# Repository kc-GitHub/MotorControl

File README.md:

Firmware HM Motor-Control
===================================

#Changelog#

## First Version: 0.01 (Beta)##
 * First Commit

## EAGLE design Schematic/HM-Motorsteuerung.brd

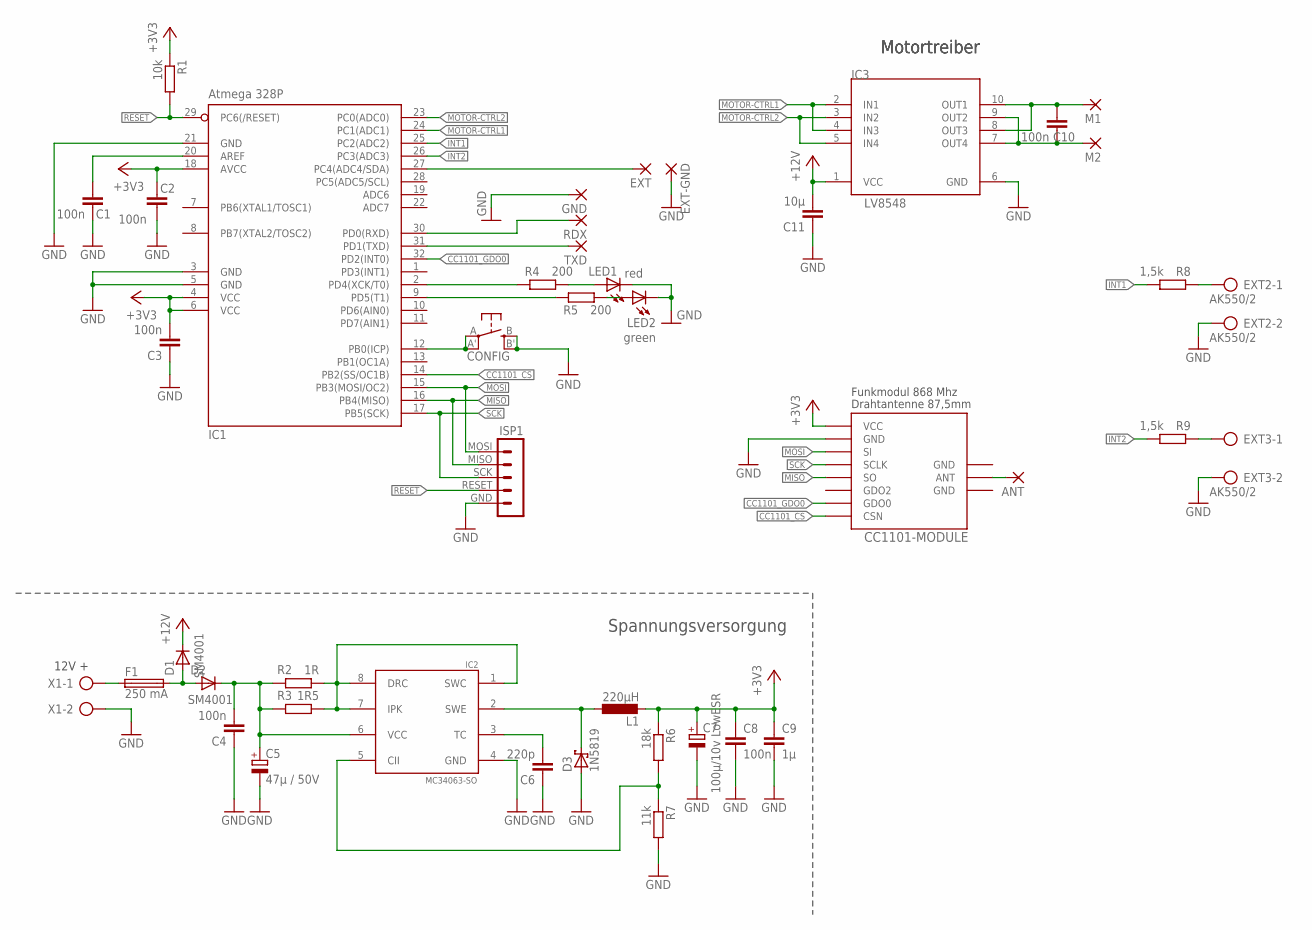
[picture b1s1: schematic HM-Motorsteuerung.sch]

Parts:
ANT: 1,6/0,8
C1, C2, C3, C4, C8, C10: 100n; C0805
C5: 47µ / 50V; E2,5-7
C6: 220p; C0805
C7: 100µ/10v LowESR; SMC_D
C9: 1µ; C0805
C11: 10µ; C1206
CC1101-MODULE: CC1101_WIRELES_MODULECC1101-SMD; CC1101
CONFIG: T1; EVQ-Q2
D1, D2: SM4001; MELF-MLL41
D3: 1N5819; SMB
EXT: WIREPADSMD1,27-254; SMD1,27-2,54
EXT2, EXT3: AK550/2
EXT-GND: WIREPADSMD1,27-254; SMD1,27-2,54
F1: 250 mA; SMD-6,1X2,6
GND: 1,6/0,8
IC1: Atmega 328P; TQFP32-08
IC2: MC34063-SO; SO8
IC3: LV8548; MFP10S; MPN LV8548MC-AH
ISP1: MYISPSMD; MYISP_SMD
L1: 220µH; L5650M
LED1: red; CHIP-LED0805
LED2: green; CHIP-LED0805
M1, M2: 1,6/0,8
R1: 10k; M0805
R2: 1R; R0805
R3: 1R5; R0805
R4, R5: 200; M0805
R6: 18k; R0805
R7: 11k; R0805
R8, R9: 1,5k; M0805
RDX: 1,6/0,8
TXD: 1,6/0,8
X1: AK550/2

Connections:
+3V3: C2.2, C3.2, C7.+, C8.1, C9.1, CC1101-MODULE.VCC, IC1.4 (VCC), IC1.6 (VCC), IC1.18 (AVCC), L1.2, R1.1, R6.1
CC1101_CS: CC1101-MODULE.CSN, IC1.14 (PB2(SS/OC1B))
CC1101_GDO0: CC1101-MODULE.GD00 (GDO0), IC1.32 (PD2(INT0))
D4: IC1.2 (PD4(XCK/T0)), R4.1
D8: CONFIG.A, CONFIG.A' (P1), IC1.12 (PB0(ICP))
GND: C1.1, C2.1, C3.1, C4.1, C5.-, C6.1, C7.-, C8.2, C9.2, C11.1, CC1101-MODULE.GND, CC1101-MODULE.GND_0 (GND), CC1101-MODULE.GND_1 (GND), CONFIG.B (S), CONFIG.B' (S1), D3.A, EXT2.2, EXT3.2, EXT-GND.1, GND.1, IC1.3 (GND), IC1.5 (GND), IC1.21 (GND), IC2.4 (GND), IC3.6 (GND), ISP1.GND, LED1.C, LED2.C, R7.2, X1.2
INT1: IC1.25 (PC2(ADC2)), R8.2
INT2: IC1.26 (PC3(ADC3)), R9.2
MISO: CC1101-MODULE.SO, IC1.16 (PB4(MISO)), ISP1.MISO
MOSI: CC1101-MODULE.SI, IC1.15 (PB3(MOSI/OC2)), ISP1.MOSI
MOTOR-CTRL1: IC1.24 (PC1(ADC1)), IC3.2 (IN1), IC3.4 (IN3)
MOTOR-CTRL2: IC1.23 (PC0(ADC0)), IC3.3 (IN2), IC3.5 (IN4)
unnamed: F1.1, X1.1
unnamed: EXT2.1, R8.1
unnamed: LED2.A, R5.2
unnamed: LED1.A, R4.2
unnamed: ANT.1, CC1101-MODULE.ANT
unnamed: EXT3.1, R9.1
unnamed: C10.2, IC3.8 (OUT3), IC3.10 (OUT1), M1.1
unnamed: C10.1, IC3.7 (OUT4), IC3.9 (OUT2), M2.1
unnamed: IC1.9 (PD5(T1)), R5.1
unnamed: EXT.1, IC1.27 (PC4(ADC4/SDA))
unnamed: C1.2, IC1.20 (AREF)
unnamed: D1.A, D2.A, F1.2
unnamed: IC2.1 (SWC), IC2.7 (IPK), IC2.8 (DRC), R2.1, R3.1
unnamed: C4.2, C5.+, D2.C, IC2.6 (VCC), R2.2, R3.2
unnamed: IC2.5 (CII), R6.2, R7.1
unnamed: C6.2, IC2.3 (TC)
unnamed: D3.C, IC2.2 (SWE), L1.1
RESET: IC1.29 (PC6(/RESET)), ISP1.RESET, R1.2
RXD: IC1.30 (PD0(RXD)), RDX.1
SCK: CC1101-MODULE.SCLK, IC1.17 (PB5(SCK)), ISP1.SCK
TXD: IC1.31 (PD1(TXD)), TXD.1
VCC-MOTOR: C11.2, D1.C, IC3.1 (VCC)

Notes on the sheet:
12V +
Spannungsversorgung
Funkmodul 868 Mhz
Drahtantenne 87,5mm
Motortreiber

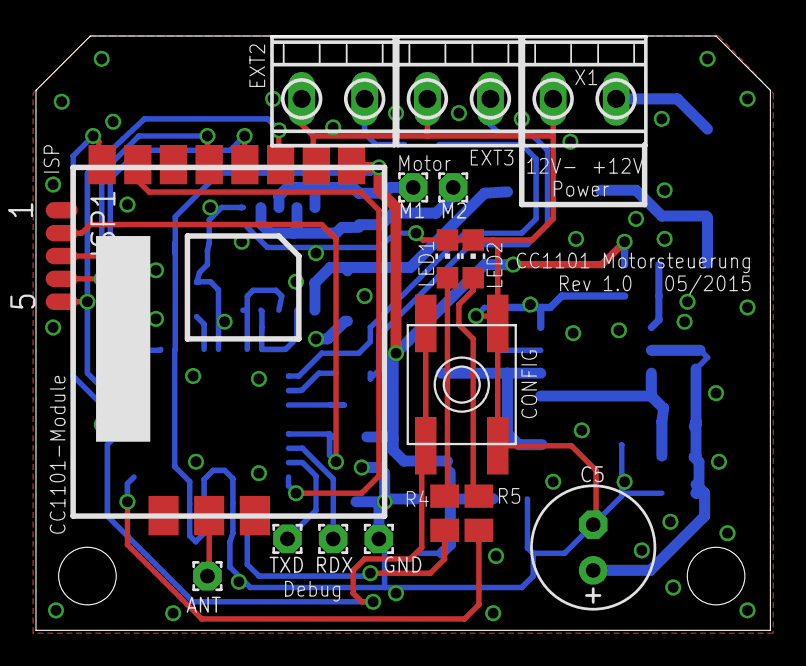
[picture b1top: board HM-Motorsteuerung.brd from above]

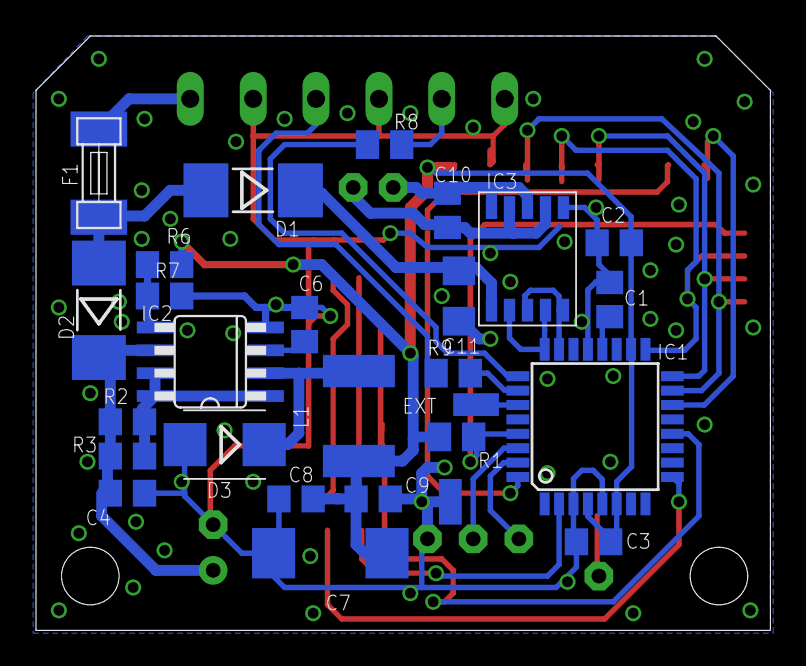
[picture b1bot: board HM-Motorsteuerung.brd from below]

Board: 2 copper layers, 40.8 x 33.0 mm, 44 parts (27 on the bottom side), 34 nets.

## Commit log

2016-03-28 First Commit with some spechial AskSin-Lib modifications Todo: Remove spechial AskSin-Lib modifications.
2016-03-28 Add readme and contrib
2016-03-28 Cleanup
2016-04-03 Fix Overflow of REFERENCE_RUNNING_TIME_BOTTOM_TOP Reverse motor direction Motor stop after 1 seconds without impulses
2016-04-03 Add Schematic
2016-04-04 Add 3D-Print-Files
2016-04-04 Add some Images
2016-04-04 Update STL-Files
2016-04-06 add processing of STOP_CHANGE message
2016-04-06 Move dclaration of s_pcINT stuct
2016-04-06 wrap #ifndef USE_OWN_ISR_PCINT[0-2]_vect around (ISR PCINT0[-2]_vec), so we can disable built ISR functions an can define own one
2016-04-06 - increase debounce time - add own ISR PCINT1_vect for counting impulses and detect end switch - rework impulse counting and end switch detection - implement processing of stop _change message - clea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
2016-04-06 - decrease send status intervall while running to 2 seconds - fix send status - fix wrong send status after pressed peered remote keys
2016-04-06 update todo's
2016-04-07 Fix position calculation
2016-04-07 Increase version of AskSin-Lib
2016-04-07 Add posibility ro read HM-ID and HM-Serial from Bootloader section
2016-04-07 Change definition of travelMax to int16_t add motorbreak at stop
2016-04-07 make shure position can not > 100% so prevent overflow to 0xFF
2016-04-08 remember last position and state in eeprom so we can get this values after switch power off
2016-04-09 Add option to reverse the motor direction
2016-04-09 Fix in a AS_DBG section
2016-04-14 Some optimations
2016-04-14 Implement processing of action commands (set, switch remote, ...) in AES mode
2016-04-14 Remove own NewAskSin Lib Add NewAskSin-Lib as submodule remove dependencies to cmBlind add new module cmMyBlind
2016-04-15 Update submodule
2016-04-15 Fix bugs on travel counting
2016-04-15 More debugs + Cleanup
2016-04-15 Cleanup and optimations so we can save some progmem
2016-04-15 Cleanup, optimations, spelling
2016-04-16 Cleanup and optimations so we can save some progmem again
2016-04-16 Fixes in AskSin-Lib -> Update Subrepo
2016-04-18 Add processing of ENTER_BOOTLOADER message in Asksin-Lib -> Update Subrepo
2016-04-18 Update Subrepo
